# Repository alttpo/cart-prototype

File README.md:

# cart-prototype
SNES prototype cart for 3v3 experimentation

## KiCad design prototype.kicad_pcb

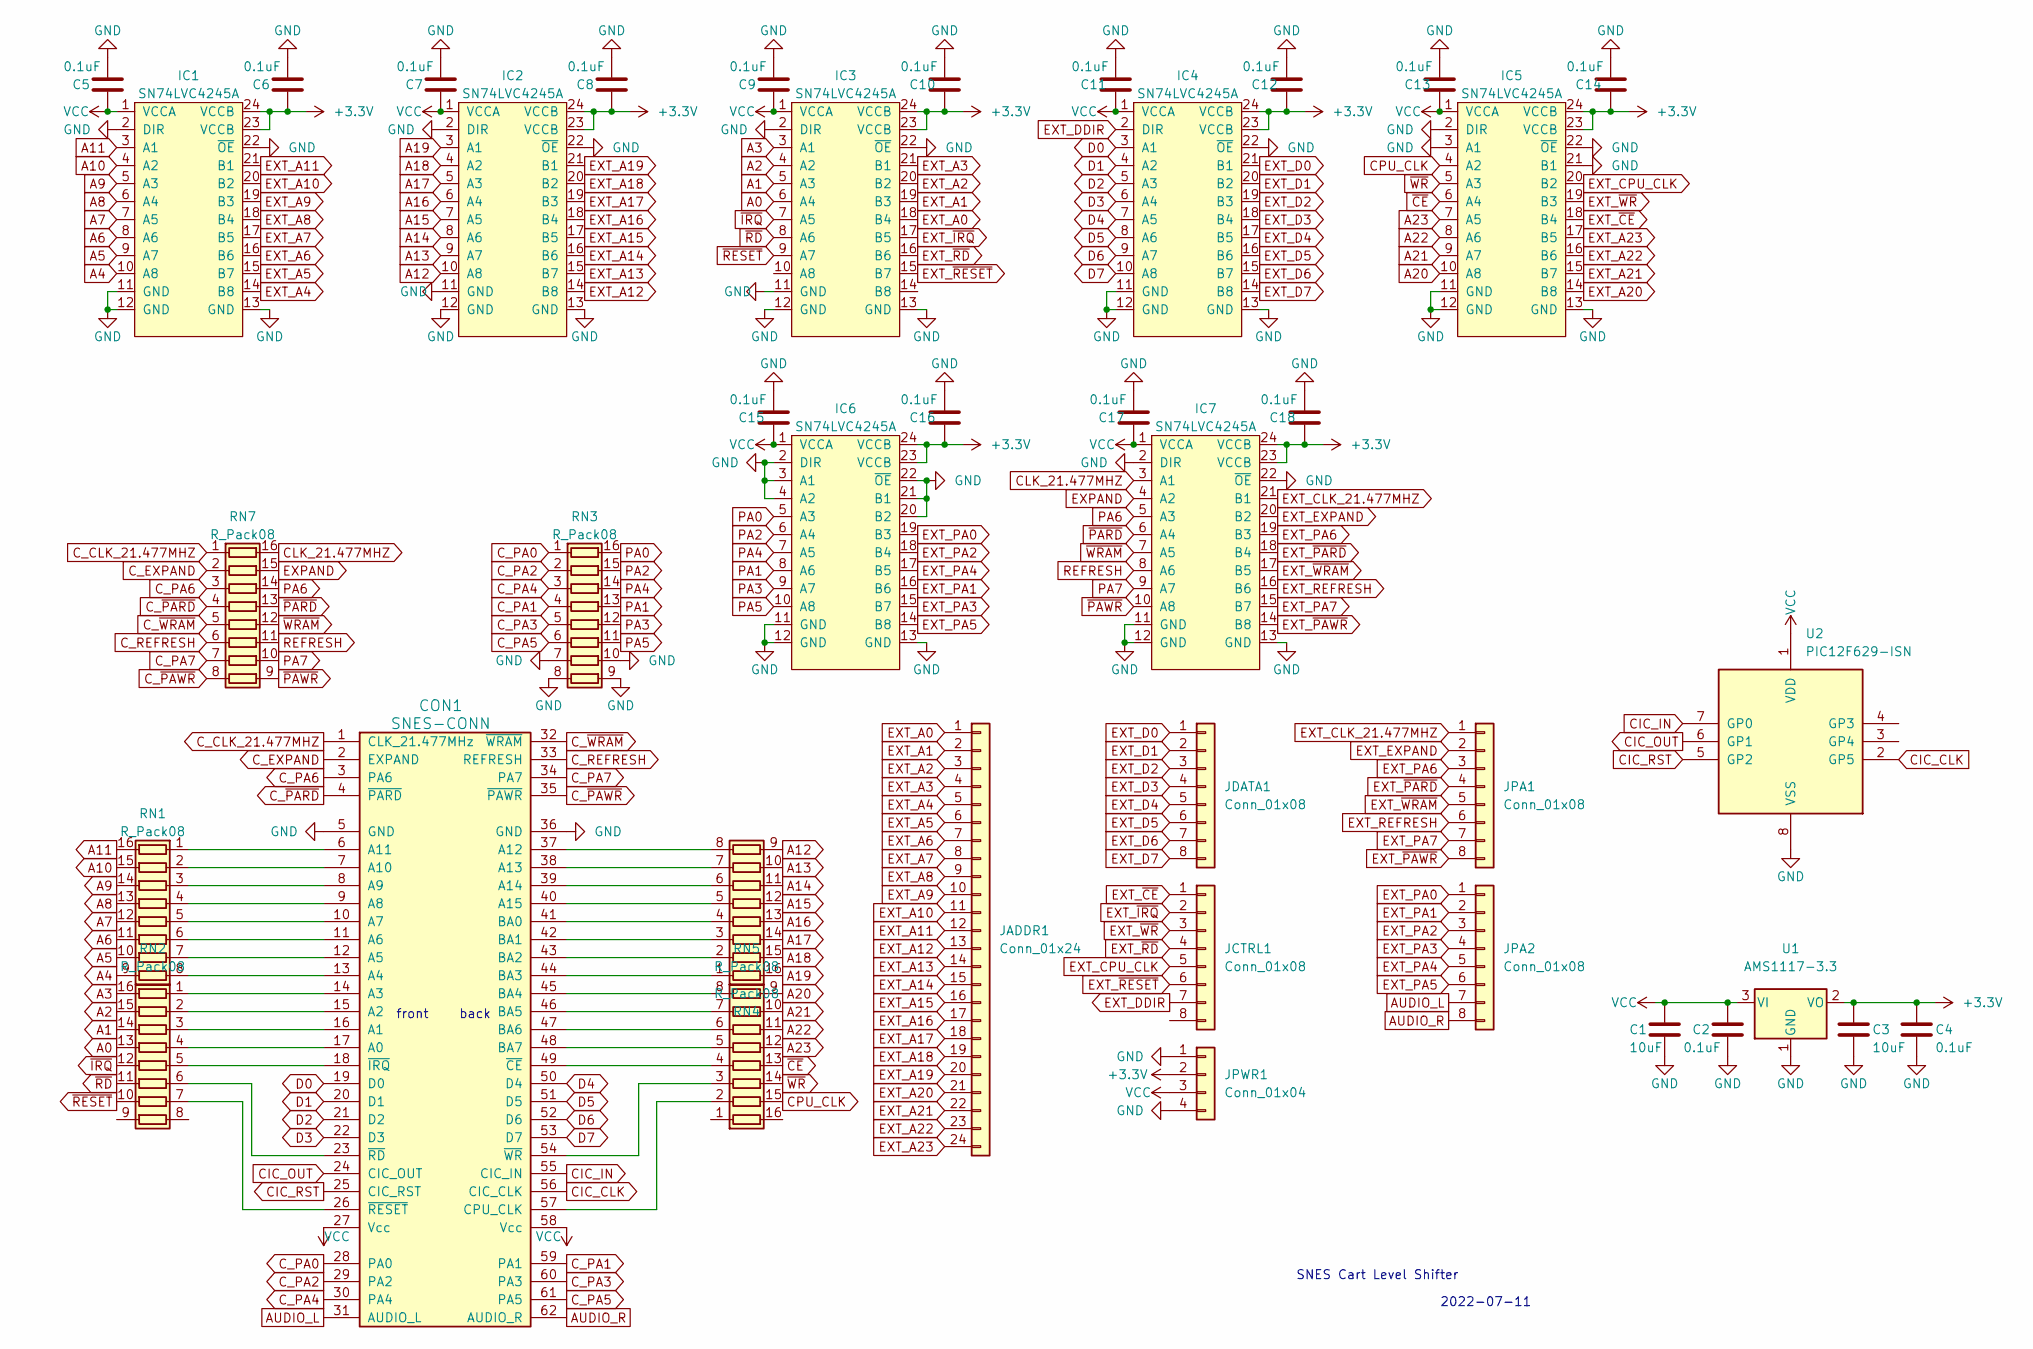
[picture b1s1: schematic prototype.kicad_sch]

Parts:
C1, C3: 10uF; C_0805_2012Metric_Pad1.18x1.45mm_HandSolder
C2, C4, C5, C6, C7, C8, C9, C10, C11, C12, C13, C14, C15, C16, C17, C18: 0.1uF; C_0805_2012Metric_Pad1.18x1.45mm_HandSolder
CON1: SNES-CONN; SNESCART_EXT2_SMTUSB
IC1, IC2, IC3, IC4, IC5, IC6, IC7: SN74LVC4245A; SOIC-24W_7.5x15.4mm_P1.27mm; Farnell 1236393
JADDR1: Conn_01x24; PinHeader_1x24_P2.54mm_Horizontal
JCTRL1: Conn_01x08; PinHeader_1x08_P2.54mm_Horizontal
JDATA1: Conn_01x08; PinHeader_1x08_P2.54mm_Horizontal
JPA1, JPA2: Conn_01x08; PinHeader_1x08_P2.54mm_Horizontal
JPWR1: Conn_01x04; PinHeader_1x04_P2.54mm_Horizontal
RN1, RN2, RN3, RN4, RN5, RN7: R_Pack08; SOIC-16_3.9x9.9mm_P1.27mm
U1: AMS1117-3.3; SOT-223-3_TabPin2
U2: PIC12F629-ISN; DIP-8_W7.62mm

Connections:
+3.3V: C3.1, C4.1, C6.1, C8.1, C10.1, C12.1, C14.1, C16.1, C18.1, IC1.23 (VCCB), IC1.24 (VCCB), IC2.23 (VCCB), IC2.24 (VCCB), IC3.23 (VCCB), IC3.24 (VCCB), IC4.23 (VCCB), IC4.24 (VCCB), IC5.23 (VCCB), IC5.24 (VCCB), IC6.23 (VCCB), IC6.24 (VCCB), IC7.23 (VCCB), IC7.24 (VCCB), JPWR1.2, U1.2 (VO)
A0: IC3.6 (A4), RN2.13 (R4.2)
A1: IC3.5 (A3), RN2.14 (R3.2)
A2: IC3.4 (A2), RN2.15 (R2.2)
A3: IC3.3 (A1), RN2.16 (R1.2)
A4: IC1.10 (A8), RN1.9 (R8.2)
A5: IC1.9 (A7), RN1.10 (R7.2)
A6: IC1.8 (A6), RN1.11 (R6.2)
A7: IC1.7 (A5), RN1.12 (R5.2)
A8: IC1.6 (A4), RN1.13 (R4.2)
A9: IC1.5 (A3), RN1.14 (R3.2)
A10: IC1.4 (A2), RN1.15 (R2.2)
A11: IC1.3 (A1), RN1.16 (R1.2)
A12: IC2.10 (A8), RN4.9 (R8.2)
A13: IC2.9 (A7), RN4.10 (R7.2)
A14: IC2.8 (A6), RN4.11 (R6.2)
A15: IC2.7 (A5), RN4.12 (R5.2)
A16: IC2.6 (A4), RN4.13 (R4.2)
A17: IC2.5 (A3), RN4.14 (R3.2)
A18: IC2.4 (A2), RN4.15 (R2.2)
A19: IC2.3 (A1), RN4.16 (R1.2)
A20: IC5.10 (A8), RN5.9 (R8.2)
A21: IC5.9 (A7), RN5.10 (R7.2)
A22: IC5.8 (A6), RN5.11 (R6.2)
A23: IC5.7 (A5), RN5.12 (R5.2)
AUDIO_L: CON1.31 (AUDIO_L), JPA2.7
AUDIO_R: CON1.62 (AUDIO_R), JPA2.8
CIC_CLK: CON1.56 (CIC_CLK), U2.2 (GP5)
CIC_IN: CON1.55 (CIC_IN), U2.7 (GP0)
CIC_OUT: CON1.24 (CIC_OUT), U2.6 (GP1)
CIC_RST: CON1.25 (CIC_RST), U2.5 (GP2)
CLK_21.477MHZ: IC7.3 (A1), RN7.16 (R1.2)
CPU_CLK: IC5.4 (A2), RN5.15 (R2.2)
C_CLK_21.477MHZ: CON1.1 (CLK_21.477MHz), RN7.1 (R1.1)
C_EXPAND: CON1.2 (EXPAND), RN7.2 (R2.1)
C_PA0: CON1.28 (PA0), RN3.1 (R1.1)
C_PA1: CON1.59 (PA1), RN3.4 (R4.1)
C_PA2: CON1.29 (PA2), RN3.2 (R2.1)
C_PA3: CON1.60 (PA3), RN3.5 (R5.1)
C_PA4: CON1.30 (PA4), RN3.3 (R3.1)
C_PA5: CON1.61 (PA5), RN3.6 (R6.1)
C_PA6: CON1.3 (PA6), RN7.3 (R3.1)
C_PA7: CON1.34 (PA7), RN7.7 (R7.1)
C_REFRESH: CON1.33 (REFRESH), RN7.6 (R6.1)
C_~PARD: CON1.4 (~PARD), RN7.4 (R4.1)
C_~PAWR: CON1.35 (~PAWR), RN7.8 (R8.1)
C_~WRAM: CON1.32 (~WRAM), RN7.5 (R5.1)
D0: CON1.19 (D0), IC4.3 (A1)
D1: CON1.20 (D1), IC4.4 (A2)
D2: CON1.21 (D2), IC4.5 (A3)
D3: CON1.22 (D3), IC4.6 (A4)
D4: CON1.50 (D4), IC4.7 (A5)
D5: CON1.51 (D5), IC4.8 (A6)
D6: CON1.52 (D6), IC4.9 (A7)
D7: CON1.53 (D7), IC4.10 (A8)
EXPAND: IC7.4 (A2), RN7.15 (R2.2)
EXT_A0: IC3.18 (B4), JADDR1.1
EXT_A1: IC3.19 (B3), JADDR1.2
EXT_A2: IC3.20 (B2), JADDR1.3
EXT_A3: IC3.21 (B1), JADDR1.4
EXT_A4: IC1.14 (B8), JADDR1.5
EXT_A5: IC1.15 (B7), JADDR1.6
EXT_A6: IC1.16 (B6), JADDR1.7
EXT_A7: IC1.17 (B5), JADDR1.8
EXT_A8: IC1.18 (B4), JADDR1.9
EXT_A9: IC1.19 (B3), JADDR1.10
EXT_A10: IC1.20 (B2), JADDR1.11
EXT_A11: IC1.21 (B1), JADDR1.12
EXT_A12: IC2.14 (B8), JADDR1.13
EXT_A13: IC2.15 (B7), JADDR1.14
EXT_A14: IC2.16 (B6), JADDR1.15
EXT_A15: IC2.17 (B5), JADDR1.16
EXT_A16: IC2.18 (B4), JADDR1.17
EXT_A17: IC2.19 (B3), JADDR1.18
EXT_A18: IC2.20 (B2), JADDR1.19
EXT_A19: IC2.21 (B1), JADDR1.20
EXT_A20: IC5.14 (B8), JADDR1.21
EXT_A21: IC5.15 (B7), JADDR1.22
EXT_A22: IC5.16 (B6), JADDR1.23
EXT_A23: IC5.17 (B5), JADDR1.24
EXT_CLK_21.477MHZ: IC7.21 (B1), JPA1.1
EXT_CPU_CLK: IC5.20 (B2), JCTRL1.5
EXT_D0: IC4.21 (B1), JDATA1.1
EXT_D1: IC4.20 (B2), JDATA1.2
EXT_D2: IC4.19 (B3), JDATA1.3
EXT_D3: IC4.18 (B4), JDATA1.4
EXT_D4: IC4.17 (B5), JDATA1.5
EXT_D5: IC4.16 (B6), JDATA1.6
EXT_D6: IC4.15 (B7), JDATA1.7
EXT_D7: IC4.14 (B8), JDATA1.8
EXT_DDIR: IC4.2 (DIR), JCTRL1.7
EXT_EXPAND: IC7.20 (B2), JPA1.2
EXT_PA0: IC6.19 (B3), JPA2.1
EXT_PA1: IC6.16 (B6), JPA2.2
EXT_PA2: IC6.18 (B4), JPA2.3
EXT_PA3: IC6.15 (B7), JPA2.4
EXT_PA4: IC6.17 (B5), JPA2.5
EXT_PA5: IC6.14 (B8), JPA2.6
EXT_PA6: IC7.19 (B3), JPA1.3
EXT_PA7: IC7.15 (B7), JPA1.7
EXT_REFRESH: IC7.16 (B6), JPA1.6
EXT_~CE: IC5.18 (B4), JCTRL1.1
EXT_~IRQ: IC3.17 (B5), JCTRL1.2
EXT_~PARD: IC7.18 (B4), JPA1.4
EXT_~PAWR: IC7.14 (B8), JPA1.8
EXT_~RD: IC3.16 (B6), JCTRL1.4
EXT_~RESET: IC3.15 (B7), JCTRL1.6
EXT_~WRAM: IC7.17 (B5), JPA1.5
EXT_~WR: IC5.19 (B3), JCTRL1.3
GND: C1.2, C2.2, C3.2, C4.2, C5.2, C6.2, C7.2, C8.2, C9.2, C10.2, C11.2, C12.2, C13.2, C14.2, C15.2, C16.2, C17.2, C18.2, CON1.5 (GND), CON1.36 (GND), IC1.2 (DIR), IC1.11 (GND), IC1.12 (GND), IC1.13 (GND), IC1.22 (~OE), IC2.2 (DIR), IC2.11 (GND), IC2.12 (GND), IC2.13 (GND), IC2.22 (~OE), IC3.2 (DIR), IC3.11 (GND), IC3.12 (GND), IC3.13 (GND), IC3.22 (~OE), IC4.11 (GND), IC4.12 (GND), IC4.13 (GND), IC4.22 (~OE), IC5.2 (DIR), IC5.3 (A1), IC5.11 (GND), IC5.12 (GND), IC5.13 (GND), IC5.21 (B1), IC5.22 (~OE), IC6.2 (DIR), IC6.3 (A1), IC6.4 (A2), IC6.11 (GND), IC6.12 (GND), IC6.13 (GND), IC6.20 (B2), IC6.21 (B1), IC6.22 (~OE), IC7.2 (DIR), IC7.11 (GND), IC7.12 (GND), IC7.13 (GND), IC7.22 (~OE), JPWR1.1, JPWR1.4, RN3.7 (R7.1), RN3.8 (R8.1), RN3.9 (R8.2), RN3.10 (R7.2), U1.1 (GND), U2.8 (VSS)
unnamed: CON1.6 (A11), RN1.1 (R1.1)
unnamed: CON1.7 (A10), RN1.2 (R2.1)
unnamed: CON1.8 (A9), RN1.3 (R3.1)
unnamed: CON1.9 (A8), RN1.4 (R4.1)
unnamed: CON1.10 (A7), RN1.5 (R5.1)
unnamed: CON1.11 (A6), RN1.6 (R6.1)
unnamed: CON1.12 (A5), RN1.7 (R7.1)
unnamed: CON1.13 (A4), RN1.8 (R8.1)
unnamed: CON1.14 (A3), RN2.1 (R1.1)
unnamed: CON1.15 (A2), RN2.2 (R2.1)
unnamed: CON1.16 (A1), RN2.3 (R3.1)
unnamed: CON1.17 (A0), RN2.4 (R4.1)
unnamed: CON1.18 (~IRQ), RN2.5 (R5.1)
unnamed: CON1.23 (~RD), RN2.6 (R6.1)
unnamed: CON1.26 (~RESET), RN2.7 (R7.1)
unnamed: CON1.37 (A12), RN4.8 (R8.1)
unnamed: CON1.38 (A13), RN4.7 (R7.1)
unnamed: CON1.39 (A14), RN4.6 (R6.1)
unnamed: CON1.40 (A15), RN4.5 (R5.1)
unnamed: CON1.41 (BA0), RN4.4 (R4.1)
unnamed: CON1.42 (BA1), RN4.3 (R3.1)
unnamed: CON1.43 (BA2), RN4.2 (R2.1)
unnamed: CON1.44 (BA3), RN4.1 (R1.1)
unnamed: CON1.45 (BA4), RN5.8 (R8.1)
unnamed: CON1.46 (BA5), RN5.7 (R7.1)
unnamed: CON1.47 (BA6), RN5.6 (R6.1)
unnamed: CON1.48 (BA7), RN5.5 (R5.1)
unnamed: CON1.49 (~CE), RN5.4 (R4.1)
unnamed: CON1.54 (~WR), RN5.3 (R3.1)
unnamed: CON1.57 (CPU_CLK), RN5.2 (R2.1)
PA0: IC6.5 (A3), RN3.16 (R1.2)
PA1: IC6.8 (A6), RN3.13 (R4.2)
PA2: IC6.6 (A4), RN3.15 (R2.2)
PA3: IC6.9 (A7), RN3.12 (R5.2)
PA4: IC6.7 (A5), RN3.14 (R3.2)
PA5: IC6.10 (A8), RN3.11 (R6.2)
PA6: IC7.5 (A3), RN7.14 (R3.2)
PA7: IC7.9 (A7), RN7.10 (R7.2)
REFRESH: IC7.8 (A6), RN7.11 (R6.2)
VCC: C1.1, C2.1, C5.1, C7.1, C9.1, C11.1, C13.1, C15.1, C17.1, CON1.27 (Vcc), CON1.58 (Vcc), IC1.1 (VCCA), IC2.1 (VCCA), IC3.1 (VCCA), IC4.1 (VCCA), IC5.1 (VCCA), IC6.1 (VCCA), IC7.1 (VCCA), JPWR1.3, U1.3 (VI), U2.1 (VDD)
~CE: IC5.6 (A4), RN5.13 (R4.2)
~IRQ: IC3.7 (A5), RN2.12 (R5.2)
~PARD: IC7.6 (A4), RN7.13 (R4.2)
~PAWR: IC7.10 (A8), RN7.9 (R8.2)
~RD: IC3.8 (A6), RN2.11 (R6.2)
~RESET: IC3.9 (A7), RN2.10 (R7.2)
~WRAM: IC7.7 (A5), RN7.12 (R5.2)
~WR: IC5.5 (A3), RN5.14 (R3.2)

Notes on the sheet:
SNES Cart Level Shifter
front
2022-07-11
back

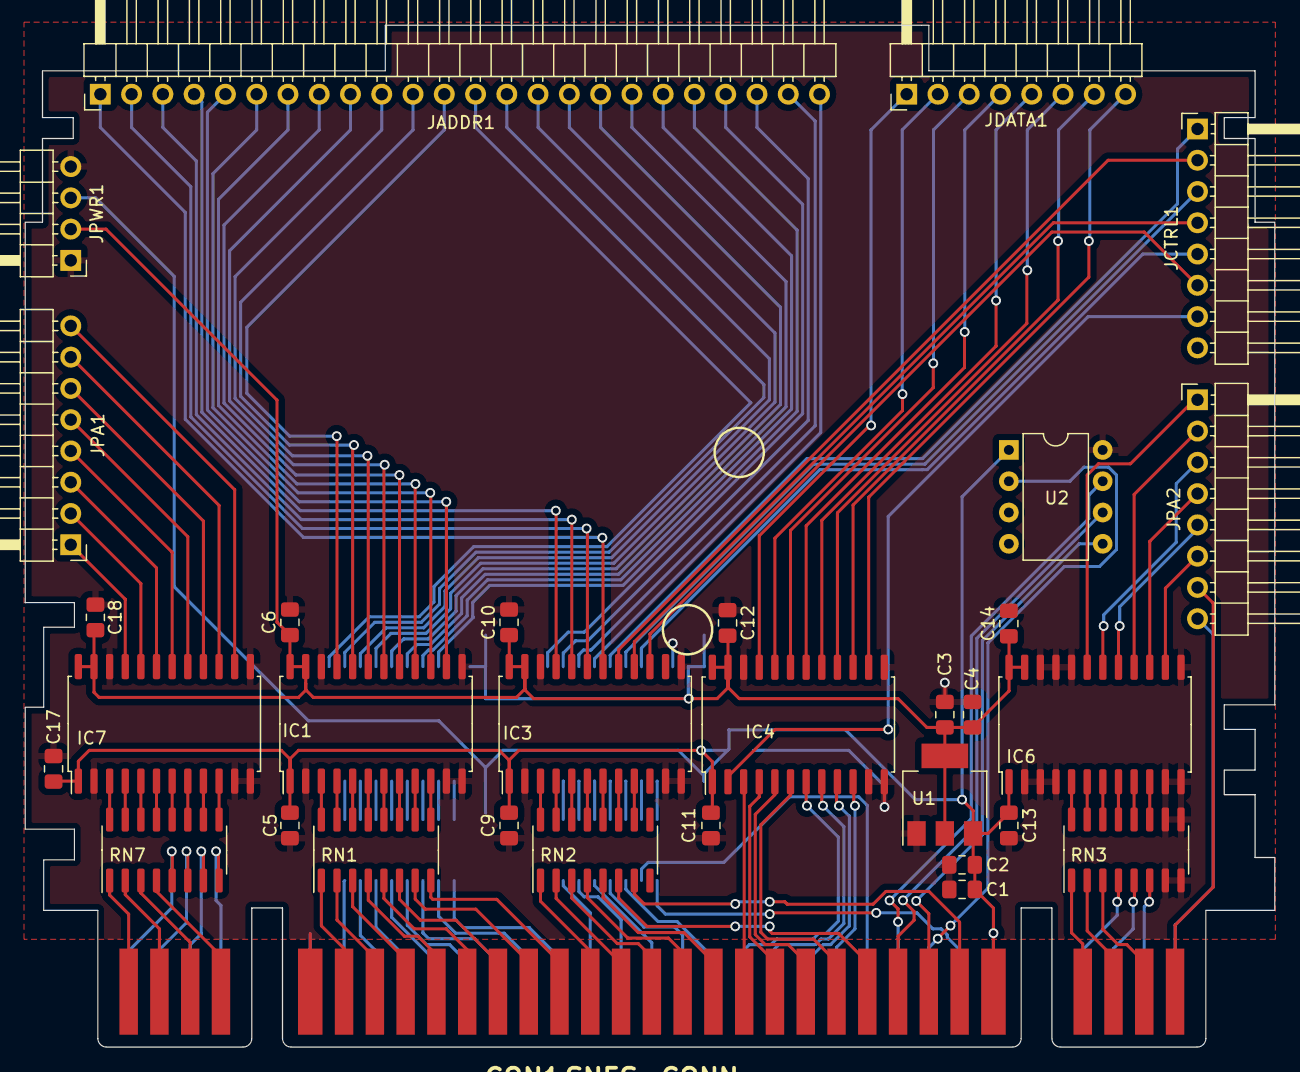
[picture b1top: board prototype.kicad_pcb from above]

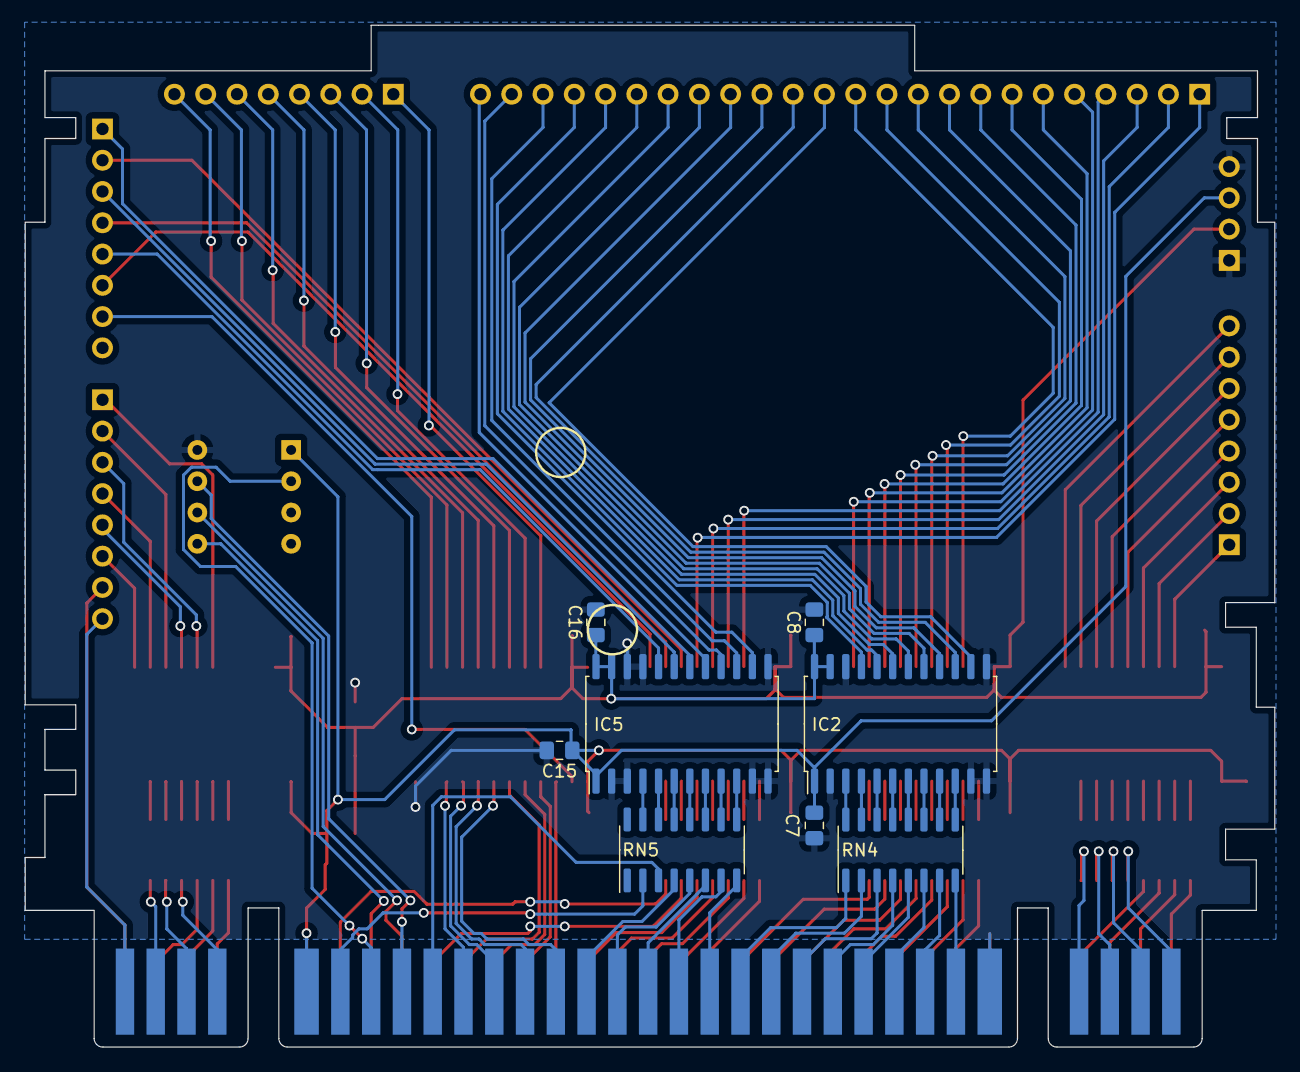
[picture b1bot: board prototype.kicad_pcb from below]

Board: 2 copper layers, 101.5 x 83.0 mm, 40 parts (8 on the bottom side), 158 nets.

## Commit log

2022-07-12 Redesign to reduce components, include PIC12 for CIC implementation
2022-07-12 Initial commit of prototype SNES edge connector board with level shifters
2022-07-12 Added 1206 footprints to caps
2022-07-12 Add resistor networks in between edge connectors and level shifters
2022-07-12 Add 3V3 voltage regulator
2022-07-13 Routed PCB; fixed up labels on schematic for proper input/output direction; added back in IRQ and RESET as inputs, can easily pull down with mosfet later
2022-07-13 Added screenshots of current design
2022-07-13 Routed new connector dedicated to power pins; routed DDIR pin to header
2022-07-13 Updated screenshots
